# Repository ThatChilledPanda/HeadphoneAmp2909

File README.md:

# HeadphoneAmp2909
Desktop USB headphone DAC and amp. USB powered

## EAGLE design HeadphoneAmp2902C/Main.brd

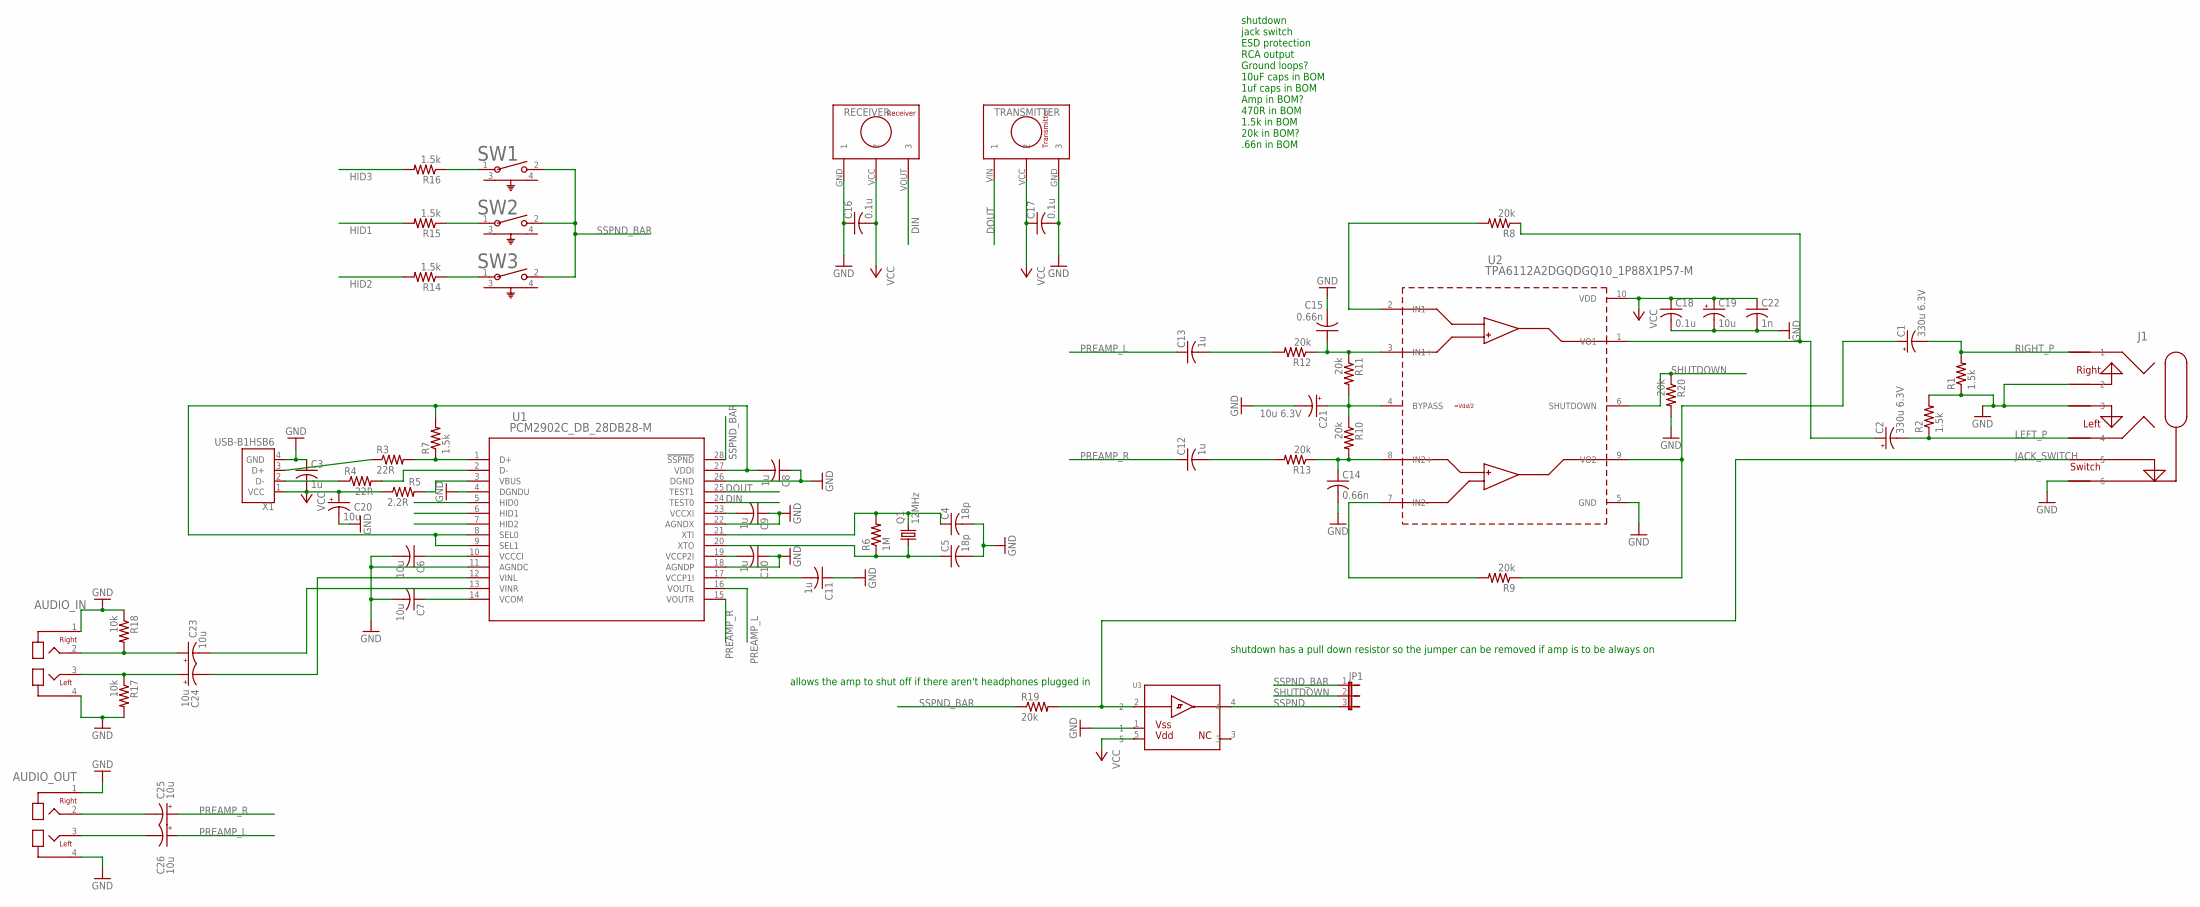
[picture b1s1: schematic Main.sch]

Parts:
AUDIO_IN: RCA-LR; CONN_J-2121
AUDIO_OUT: RCA-LR; CONN_J-2121
C1, C2: 330u 6.3V; E2,5-7
C3: 1u; C0805K
C4, C5: 18p; C0805
C6, C7: 10u; C0805
C8, C9, C10, C11, C12, C13: 1u; C0805
C14, C15: 0.66n; C0805
C16, C17, C18: 0.1u; C0805K
C19, C20, C23, C24, C25, C26: 10u; E2,5-5
C21: 10u 6.3V; E2,5-5
C22: 1n; C0805
J1: ACJS-MHDR; CONN_MHDR_AMP
JP1: JP2W
Q1: 12MHz; HC49/S
R1, R2: 1.5k; R0805
R3, R4: 22R; M0805
R5: 2.2R; M0805
R6: 1M; M0805
R7, R14, R15, R16: 1.5k; M0805
R8, R9, R10, R11, R12, R13, R19, R20: 20k; R0805
R17, R18: 10k; R0805
RECEIVER: EAPLRAA4
SW1, SW2, SW3: 1825027-8; SW2_1825027-C
TRANSMITTER: EAPLTAA4
U1: PCM2902C_DB_28DB28-M; DB28-M
U2: TPA6112A2DGQDGQ10_1P88X1P57-M; DGQ10_1P88X1P57-M
U3: TC4S584F; SOT-25___(SMV)
X1: USB-B1HSB6; OST_USB-B1HSB6

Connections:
DIN: RECEIVER.VOUT (3), U1.24 (TEST0)
DOUT: TRANSMITTER.VIN (1), U1.25 (TEST1)
GND: AUDIO_IN.1, AUDIO_IN.4 (3), AUDIO_OUT.1, AUDIO_OUT.4 (3), C3.1, C4.2, C5.2, C6.2, C7.2, C8.1, C9.1, C10.1, C11.1, C14.2, C15.2, C16.1, C17.2, C18.2, C19.-, C20.-, C21.-, C22.2, J1.1 (6), J1.2, J1.3, R1.1, R2.2, R17.2, R18.1, R20.2, RECEIVER.GND (1), TRANSMITTER.GND (3), U1.4 (DGNDU), U1.11 (AGNDC), U1.18 (AGNDP), U1.22 (AGNDX), U1.26 (DGND), U2.5 (GND), U3.1, X1.4 (GND)
HID0: U1.5 (HID0)
HID1: R15.2, U1.6 (HID1)
HID2: R14.2, U1.7 (HID2)
HID3: R16.2
JACK_SWITCH: J1.6 (5), R19.2, U3.2
LEFT_P: C2.-, J1.4, R2.1
unnamed: R3.1, X1.3 (D+)
unnamed: C8.2, R3.2, R7.1, R7.2, U1.1 (D+), U1.8 (SEL0), U1.9 (SEL1), U1.27 (VDDI)
unnamed: R4.2, U1.2 (D-)
unnamed: C2.+, R8.1, U2.1 (VO1)
unnamed: AUDIO_IN.2, C23.+, R18.2
unnamed: C1.+, R9.1, U2.9 (VO2)
unnamed: C23.-, U1.13 (VINR)
unnamed: R4.1, X1.2 (D-)
unnamed: R8.2, U2.2 (IN1-)
unnamed: C9.2, U1.23 (VCCXI)
unnamed: R5.2, U1.3 (VBUS)
unnamed: C4.1, Q1.2, R6.2, U1.21 (XTI)
unnamed: C5.1, Q1.1, R6.1, U1.20 (XTO)
unnamed: C10.2, U1.19 (VCCP2I)
unnamed: C7.1, U1.14 (VCOM)
unnamed: C6.1, U1.10 (VCCCI)
unnamed: C11.2, U1.17 (VCCP1I)
unnamed: R9.2, U2.7 (IN2-)
unnamed: C14.1, R10.2, R13.1, U2.8 (IN2+)
unnamed: C21.+, R10.1, R11.2, U2.4 (BYPASS)
unnamed: C15.1, R11.1, R12.1, U2.3 (IN1+)
unnamed: R14.1, SW3.1
unnamed: C12.2, R13.2
unnamed: C13.2, R12.2
unnamed: R15.1, SW2.1
unnamed: R16.1, SW1.1
unnamed: C24.-, U1.12 (VINL)
unnamed: AUDIO_IN.3 (4), C24.+, R17.1
unnamed: AUDIO_OUT.2, C25.-
unnamed: AUDIO_OUT.3 (4), C26.-
PREAMP_L: C13.1, C26.+, U1.16 (VOUTL)
PREAMP_R: C12.1, C25.+, U1.15 (VOUTR)
RIGHT_P: C1.-, J1.5 (1), R1.2
SHUTDOWN: JP1.2, R20.1, U2.6 (SHUTDOWN)
SSPND: JP1.3, U3.4
SSPND_BAR: JP1.1, R19.1, SW1.2, SW2.2, SW3.2, U1.28 (!SSPND)
VCC: C3.2, C16.2, C17.1, C18.1, C19.+, C20.+, C22.1, R5.1, RECEIVER.VCC (2), TRANSMITTER.VCC (2), U2.10 (VDD), U3.5, X1.1 (VCC)

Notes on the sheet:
shutdown jack switch ESD protection RCA output Ground loops? 10uF caps in BOM 1uf caps in BOM Amp in BOM? 470R in BOM 1.5k in BOM 20k in BOM? .66n in BOM
allows the amp to shut off if there aren't headphones plugged in
shutdown has a pull down resistor so the jumper can be removed if amp is to be always on

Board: 2 copper layers, 60 parts (0 on the bottom side), 44 nets, no tracks yet.

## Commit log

2020-05-07 Before PCB

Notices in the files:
parts and their libraries:
COPYRIGHT: Copyright (C) 2018 Accelerated Designs. All rights reserved
COPYRIGHT: Copyright (C) 2016 Accelerated Designs. All rights reserved
